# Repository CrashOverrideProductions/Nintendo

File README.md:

## Retro Console Parts

### **Project**: Replacement and Modification Parts for Retro Consoles 

<!-- Repo Cover Image -->

<!-- Repo Stats -->

### Details
The goal of this project is to have a collection of replacement and modification parts for retro game consoles.

<!-- To Do List -->
### Parts List
- [ ] Famicom Power Board (With Composite A/V Output)
- [x] Famicom / NES Controller PCB
- [x] Famicom HVC-NROM Cartride PCB
- [ ] SNES Controller PCB
- [ ] More to add (possibly a switch game cart pcb)

### Repo To Do List
- [ ] Tidy and Attribute Research Docs
- [ ] More to add as i think of it

<!-- Licencing Always at the Bottom -->
### Licencing 

**Creative Commons: Attribution - NonCommercial - ShareAlike 4.0 International (CC BY-NC-SA 4.0)**

**You are free to:**

**Share** — copy and redistribute the material in any medium or format

**Adapt** — remix, transform, and build upon the material

**Under the following terms:**

**Attribution** — You must give appropriate credit, provide a link to the license, and indicate if changes were made. You may do so in any reasonable manner, but not in any way that suggests the licensor endorses you or your use.

**NonCommercial** — You may not use the material for commercial purposes.

**ShareAlike** — If you remix, transform, or build upon the material, you must distribute your contributions under the same license as the original.

No additional restrictions — You may not apply legal terms or technological measures that legally restrict others from doing anything the license permits.

#####  One Last Note: 
I intent to be meticulous in using community generated documents and schematics where i cant easily reverse engineer things myself, under no circumstances will any Official/Leaked Manufacturer Interlectual Property be used in this project (e.g. Actual Schematics are covered by Copyright, however the circuit is not and therefore can be published if a third party person draws and publishes thier own reverse engineered schematic)

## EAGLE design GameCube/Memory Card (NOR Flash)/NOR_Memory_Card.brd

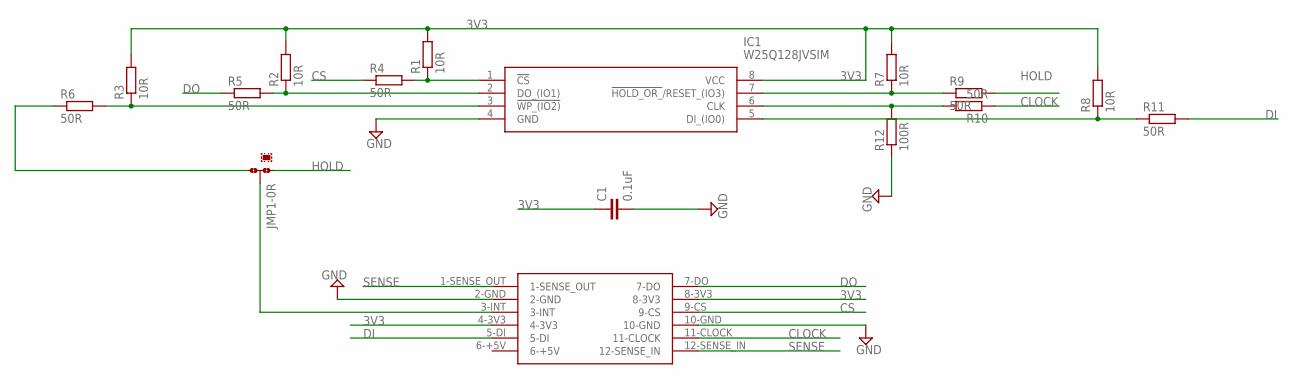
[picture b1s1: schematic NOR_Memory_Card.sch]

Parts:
C1: 0.1uF; C0805
IC1: W25Q128JVSIM; SOIC127P790X216-8N
JMP1: 0R-JUMPA; A0R-JMP
R1, R2, R3, R7, R8: 10R; R0805
R4, R5, R6, R9, R10, R11: 50R; R0805
R12: 100R; R0805
U$1: MEM_CARD_CONN

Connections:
3V3: C1.1, IC1.8 (VCC), R1.2, R2.2, R3.2, R7.2, R8.2, U$1.4-3V3, U$1.8-3V3
CLOCK: R10.1, U$1.11-CLOCK
CS: R4.1, U$1.9-CS
DI: R11.2, U$1.5-DI
DO: R5.1, U$1.7-DO
GND: C1.2, IC1.4 (GND), R12.1, U$1.2-GND, U$1.10-GND
HOLD: JMP1.1, R9.2
unnamed: IC1.7 (!HOLD_OR_!/RESET_(IO3)), R7.1, R9.1
unnamed: IC1.6 (CLK), R10.2, R12.2
unnamed: JMP1.3, R6.1
unnamed: IC1.3 (!WP_(IO2)), R3.1, R6.2
unnamed: IC1.5 (DI_(IO0)), R8.1, R11.1
unnamed: IC1.2 (DO_(IO1)), R2.1, R5.2
unnamed: IC1.1 (!CS), R1.1, R4.2
unnamed: JMP1.2, U$1.3-INT
SENSE: U$1.1-SENSE_OUT, U$1.12-SENSE_IN

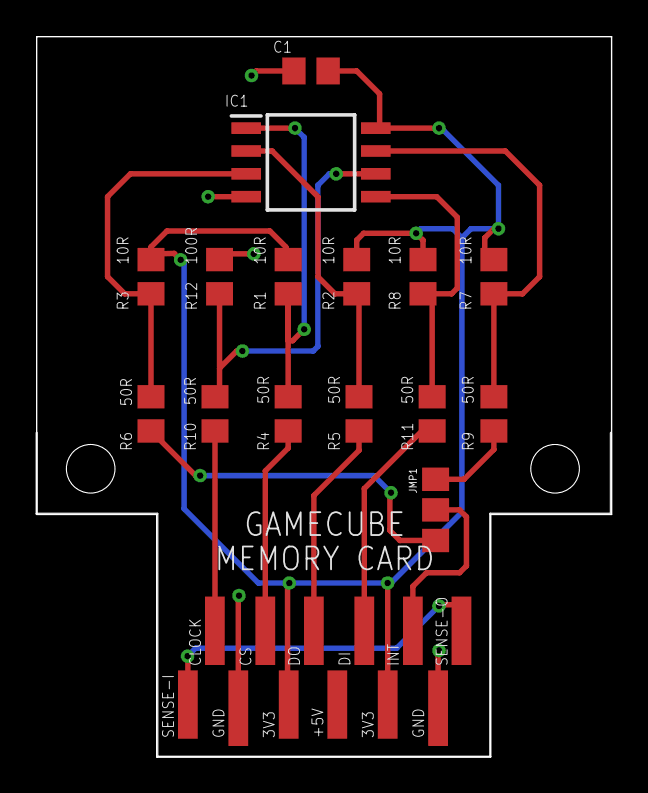
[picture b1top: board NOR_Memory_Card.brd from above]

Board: 2 copper layers, 31.9 x 40.0 mm, 16 parts (0 on the bottom side), 16 nets.

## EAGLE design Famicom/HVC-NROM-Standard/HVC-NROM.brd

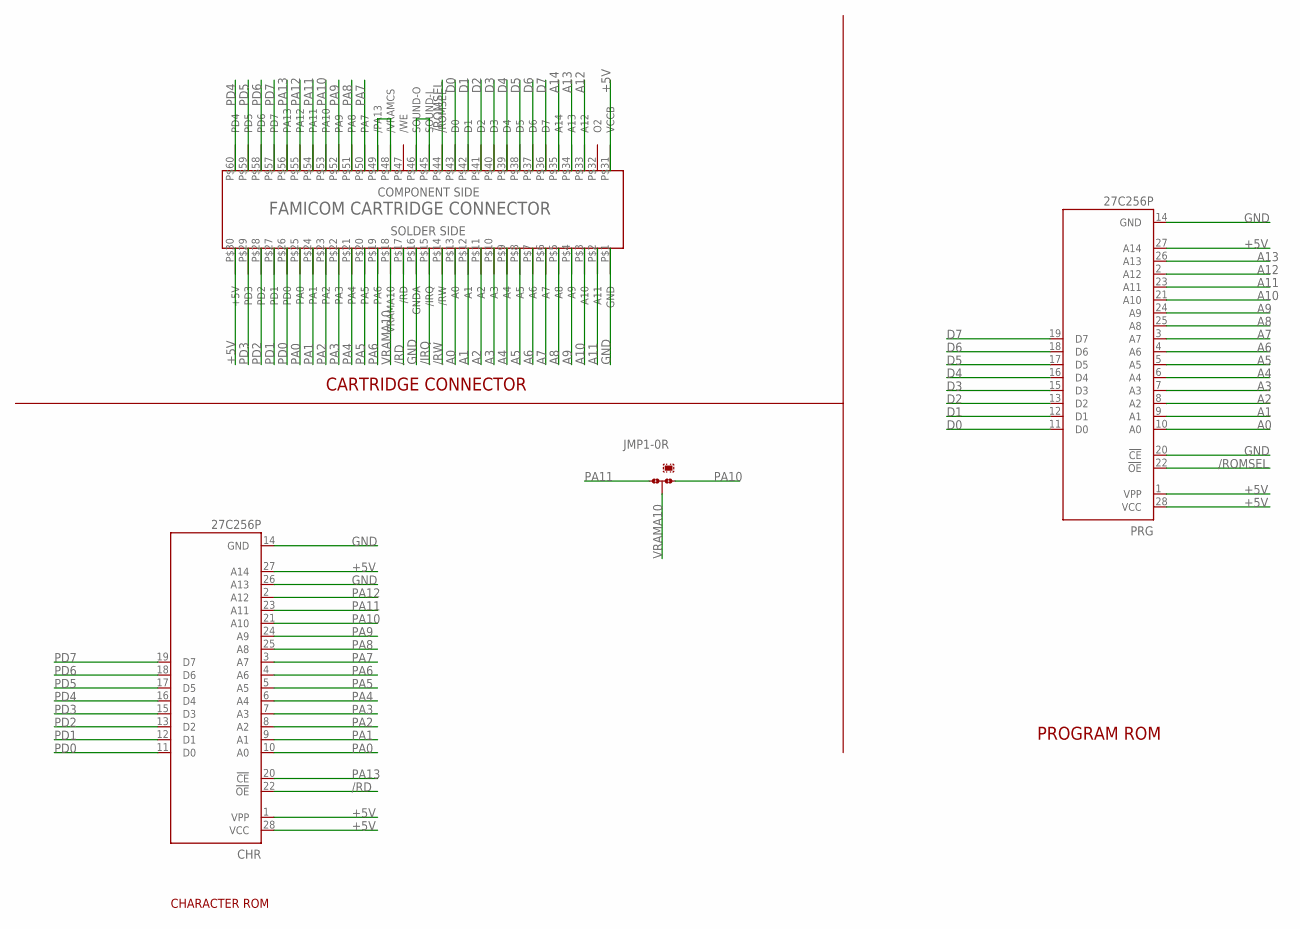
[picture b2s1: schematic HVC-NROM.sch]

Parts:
CHR: 27C256P; DIL28-6
JMP1: 0R-JUMPA; A0R-JMP
PRG: 27C256P; DIL28-6
U$1: FC-60-CART-PIN; FC-60-PIN-CART

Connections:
+5V: CHR.1 (VPP), CHR.27 (A14), CHR.28 (VCC), PRG.1 (VPP), PRG.27 (A14), PRG.28 (VCC), U$1.P$30 (+5V), U$1.P$31 (VCCB)
/IRQ: U$1.P$15 (/IRQ)
/RD: CHR.22 (!OE), U$1.P$17 (/RD)
/ROMSEL: PRG.22 (!OE), U$1.P$44 (/ROMSEL)
/RW: U$1.P$14 (/RW)
A0: PRG.10 (A0), U$1.P$13 (A0)
A1: PRG.9 (A1), U$1.P$12 (A1)
A2: PRG.8 (A2), U$1.P$11 (A2)
A3: PRG.7 (A3), U$1.P$10 (A3)
A4: PRG.6 (A4), U$1.P$9 (A4)
A5: PRG.5 (A5), U$1.P$8 (A5)
A6: PRG.4 (A6), U$1.P$7 (A6)
A7: PRG.3 (A7), U$1.P$6 (A7)
A8: PRG.25 (A8), U$1.P$5 (A8)
A9: PRG.24 (A9), U$1.P$4 (A9)
A10: PRG.21 (A10), U$1.P$3 (A10)
A11: PRG.23 (A11), U$1.P$2 (A11)
A12: PRG.2 (A12), U$1.P$33 (A12)
A13: PRG.26 (A13), U$1.P$34 (A13)
A14: U$1.P$35 (A14)
D0: PRG.11 (D0), U$1.P$43 (D0)
D1: PRG.12 (D1), U$1.P$42 (D1)
D2: PRG.13 (D2), U$1.P$41 (D2)
D3: PRG.15 (D3), U$1.P$40 (D3)
D4: PRG.16 (D4), U$1.P$39 (D4)
D5: PRG.17 (D5), U$1.P$38 (D5)
D6: PRG.18 (D6), U$1.P$37 (D6)
D7: PRG.19 (D7), U$1.P$36 (D7)
GND: CHR.14 (GND), CHR.26 (A13), PRG.14 (GND), PRG.20 (!CE), U$1.P$1 (GND), U$1.P$16 (GNDA)
unnamed: U$1.P$45 (SOUND-I), U$1.P$46 (SOUND-O)
unnamed: U$1.P$48 (/VRAMCS), U$1.P$49 (/PA13)
PA0: CHR.10 (A0), U$1.P$25 (PA0)
PA1: CHR.9 (A1), U$1.P$24 (PA1)
PA2: CHR.8 (A2), U$1.P$23 (PA2)
PA3: CHR.7 (A3), U$1.P$22 (PA3)
PA4: CHR.6 (A4), U$1.P$21 (PA4)
PA5: CHR.5 (A5), U$1.P$20 (PA5)
PA6: CHR.4 (A6), U$1.P$19 (PA6)
PA7: CHR.3 (A7), U$1.P$50 (PA7)
PA8: CHR.25 (A8), U$1.P$51 (PA8)
PA9: CHR.24 (A9), U$1.P$52 (PA9)
PA10: CHR.21 (A10), JMP1.1, U$1.P$53 (PA10)
PA11: CHR.23 (A11), JMP1.3, U$1.P$54 (PA11)
PA12: CHR.2 (A12), U$1.P$55 (PA12)
PA13: CHR.20 (!CE), U$1.P$56 (PA13)
PD0: CHR.11 (D0), U$1.P$26 (PD0)
PD1: CHR.12 (D1), U$1.P$27 (PD1)
PD2: CHR.13 (D2), U$1.P$28 (PD2)
PD3: CHR.15 (D3), U$1.P$29 (PD3)
PD4: CHR.16 (D4), U$1.P$60 (PD4)
PD5: CHR.17 (D5), U$1.P$59 (PD5)
PD6: CHR.18 (D6), U$1.P$58 (PD6)
PD7: CHR.19 (D7), U$1.P$57 (PD7)
VRAMA10: JMP1.2, U$1.P$18 (VRAMA10)

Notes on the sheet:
PROGRAM ROM
CHARACTER ROM
CARTRIDGE CONNECTOR

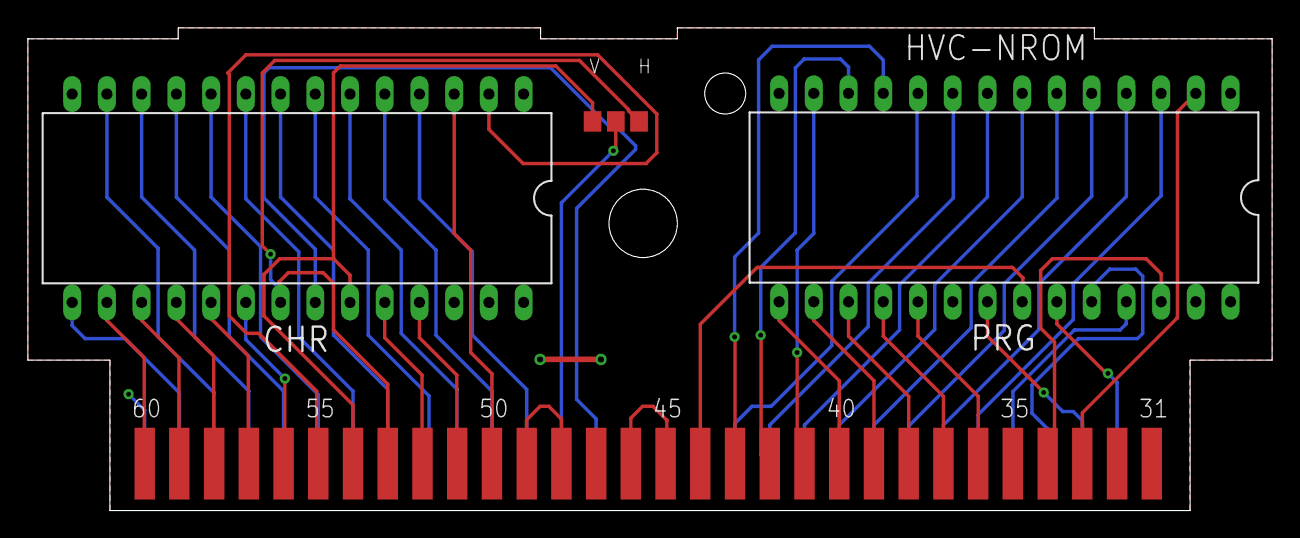
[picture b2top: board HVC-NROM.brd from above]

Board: 2 copper layers, 91.0 x 35.3 mm, 4 parts (0 on the bottom side), 51 nets.

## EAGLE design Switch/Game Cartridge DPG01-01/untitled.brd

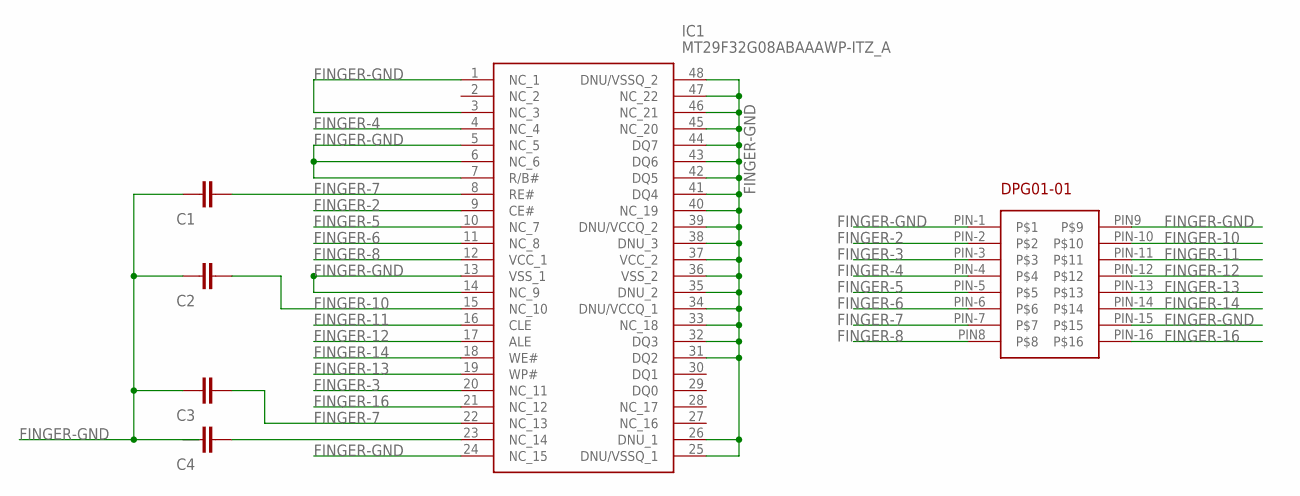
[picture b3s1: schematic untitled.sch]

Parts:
C1, C2, C3, C4: C-EUC0402; C0402
IC1: MT29F32G08ABAAAWP-ITZ_A; SOP50P2000X120-48N
U$1: DPG01-01

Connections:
FINGER-2: IC1.9 (CE#), U$1.PIN-2
FINGER-3: IC1.20 (NC_11), U$1.PIN-3
FINGER-4: IC1.4 (NC_4), U$1.PIN-4
FINGER-5: IC1.10 (NC_7), U$1.PIN-5
FINGER-6: IC1.11 (NC_8), U$1.PIN-6
FINGER-7: C1.1, C3.1, IC1.8 (RE#), IC1.22 (NC_13), U$1.PIN-7
FINGER-8: IC1.12 (VCC_1), U$1.PIN8
FINGER-10: C2.1, IC1.15 (NC_10), U$1.PIN-10
FINGER-11: IC1.16 (CLE), U$1.PIN-11
FINGER-12: IC1.17 (ALE), U$1.PIN-12
FINGER-13: IC1.19 (WP#), U$1.PIN-13
FINGER-14: IC1.18 (WE#), U$1.PIN-14
FINGER-16: IC1.21 (NC_12), U$1.PIN-16
FINGER-GND: C1.2, C2.2, C3.2, C4.2, IC1.1 (NC_1), IC1.3 (NC_3), IC1.5 (NC_5), IC1.6 (NC_6), IC1.7 (R/B#), IC1.13 (VSS_1), IC1.14 (NC_9), IC1.24 (NC_15), IC1.25 (DNU/VSSQ_1), IC1.26 (DNU_1), IC1.31 (DQ2), IC1.32 (DQ3), IC1.33 (NC_18), IC1.34 (DNU/VCCQ_1), IC1.35 (DNU_2), IC1.36 (VSS_2), IC1.37 (VCC_2), IC1.38 (DNU_3), IC1.39 (DNU/VCCQ_2), IC1.40 (NC_19), IC1.41 (DQ4), IC1.42 (DQ5), IC1.43 (DQ6), IC1.44 (DQ7), IC1.45 (NC_20), IC1.46 (NC_21), IC1.47 (NC_22), IC1.48 (DNU/VSSQ_2), U$1.PIN9, U$1.PIN-1, U$1.PIN-15
unnamed: C4.1, IC1.23 (NC_14)

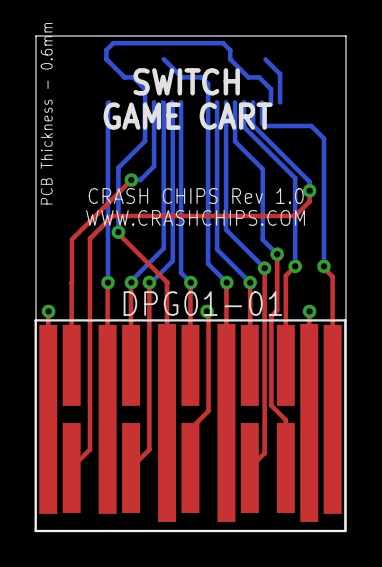
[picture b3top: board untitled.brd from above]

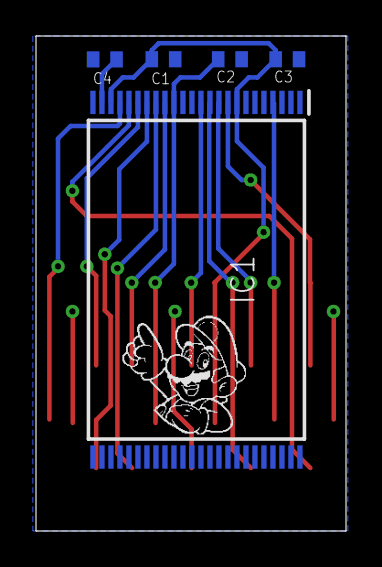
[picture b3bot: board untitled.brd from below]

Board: 2 copper layers, 17.2 x 27.5 mm, 6 parts (5 on the bottom side), 15 nets.

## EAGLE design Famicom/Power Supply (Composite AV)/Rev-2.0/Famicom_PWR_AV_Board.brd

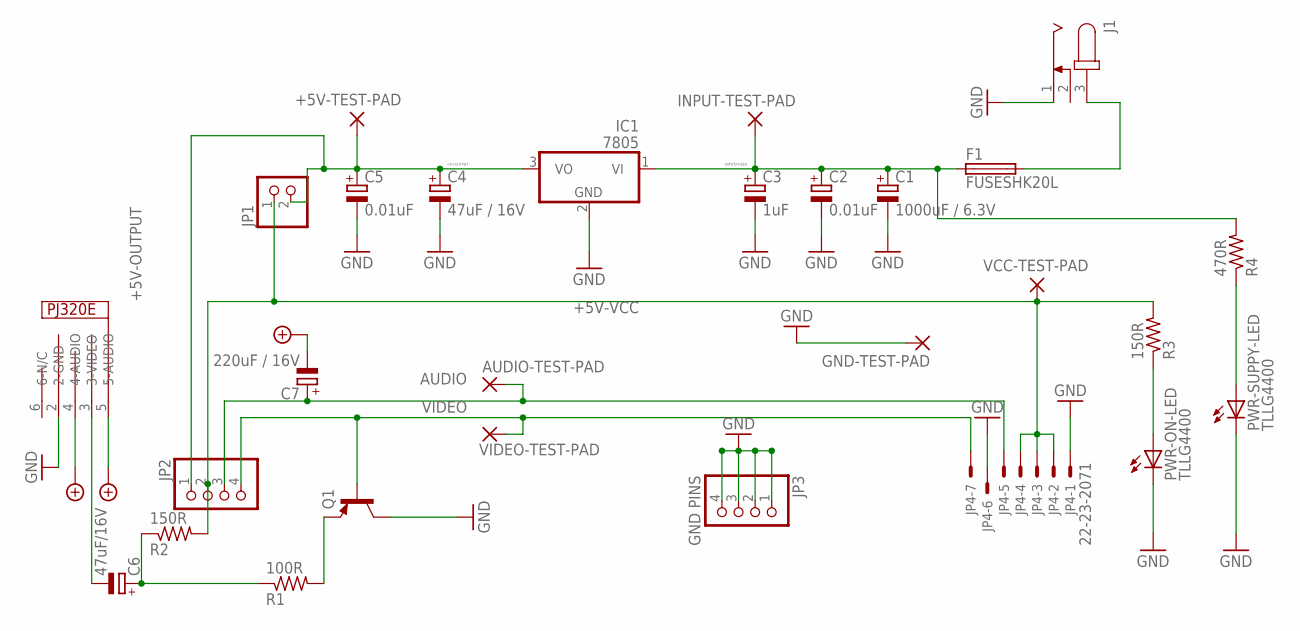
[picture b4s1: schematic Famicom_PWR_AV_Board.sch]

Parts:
+5V-TEST-PAD: WIREPAD2,15/1,0; 2,15/1,0
AUDIO-TEST-PAD: WIREPAD2,15/1,0; 2,15/1,0
C1: 1000uF / 6.3V; TAP5-45
C2, C5: 0.01uF; TAP5-45
C3: 1uF; TAP5-45
C4: 47uF / 16V; TAP5-45
C6: 47uF/16V; TAP5-45
C7: 220uF / 16V; TAP5-45
F1: FUSESHK20L; SHK20L
GND-TEST-PAD: WIREPAD2,15/1,0; 2,15/1,0
IC1: 7805; TO220V
INPUT-TEST-PAD: WIREPAD2,15/1,0; 2,15/1,0
J1: JACK-PLUG0; SPC4077
JP1: PINHD-1X2; 1X02
JP2: PINHD-1X4; 1X04
JP3: GND PINS; 1X04
JP4: 22-23-2071
PWR-ON-LED: TLLG4400; LED3MM
PWR-SUPPY-LED: TLLG4400; LED3MM
Q1: MPSA56-TO92; TO92-CBE
R1: 100R; 0204/7
R2, R3: 150R; 0204/7
R4: 470R; 0204/7
U$2: PJ320E
VCC-TEST-PAD: WIREPAD2,15/1,0; 2,15/1,0
VIDEO-TEST-PAD: WIREPAD2,15/1,0; 2,15/1,0

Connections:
+5V-OUTPUT: +5V-TEST-PAD.1, C4.+, C5.+, IC1.3 (VO), JP1.2, JP2.1
+5V-VCC: JP1.1, JP2.2, JP4.2, JP4.3, JP4.4, R2.2, R3.2, VCC-TEST-PAD.1
+9V-INPUT-UNFUSED: F1.2A (2), J1.3
AUDIO: AUDIO-TEST-PAD.1, C7.+, JP2.3, JP4.5
AUDIO_OUTPUT: C7.-, U$2.4 (4-AUDIO), U$2.5 (5-AUDIO)
GND: C1.-, C2.-, C3.-, C4.-, C5.-, GND-TEST-PAD.1, IC1.2 (GND), J1.1, JP3.1, JP3.2, JP3.3, JP3.4, JP4.1, JP4.6, PWR-ON-LED.K (C), PWR-SUPPY-LED.K (C), Q1.C, U$2.2 (2-GND)
INPUT|FUSED: C1.+, C2.+, C3.+, F1.1A (1), IC1.1 (VI), INPUT-TEST-PAD.1, R4.2
ON_LED: PWR-ON-LED.A, R3.1
SUPPLY_LED: PWR-SUPPY-LED.A, R4.1
VIDEO: JP2.4, JP4.7, Q1.B, VIDEO-TEST-PAD.1
VIDEO_AMP: C6.+, R1.1, R2.1
VIDEO_OUTPUT: C6.-, U$2.3 (3-VIDEO)
VIDEO_PREAMP: Q1.E, R1.2

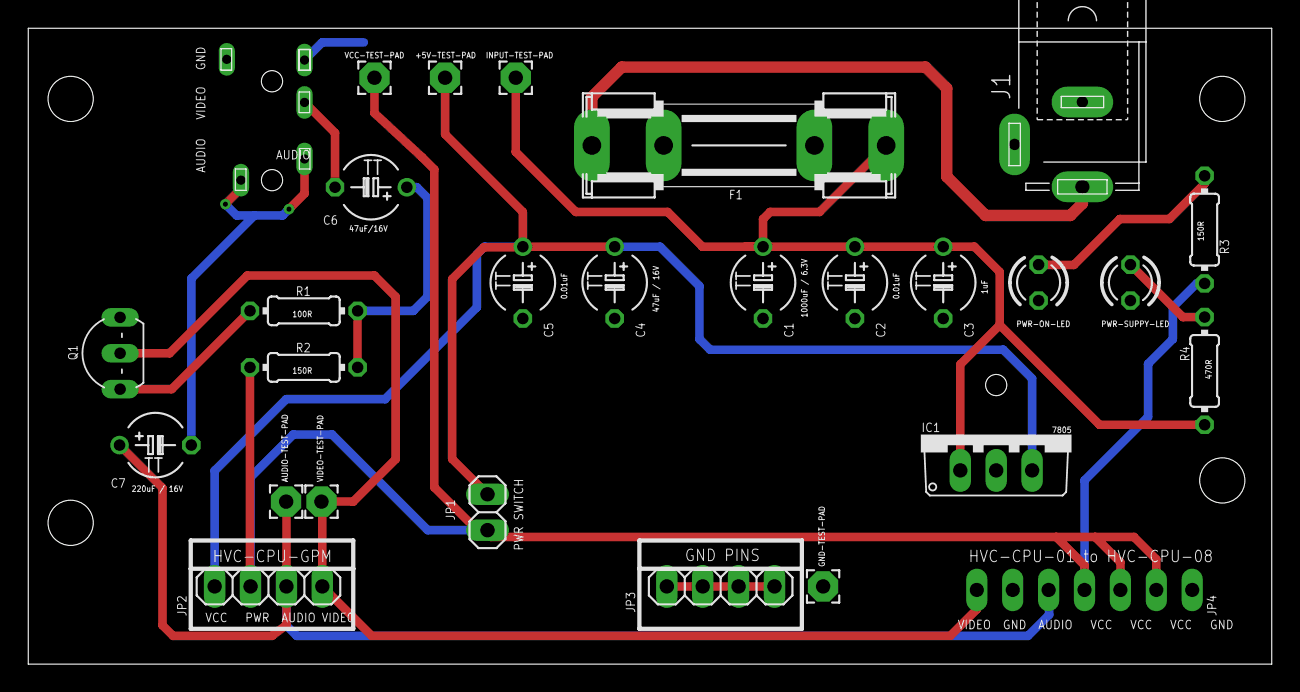
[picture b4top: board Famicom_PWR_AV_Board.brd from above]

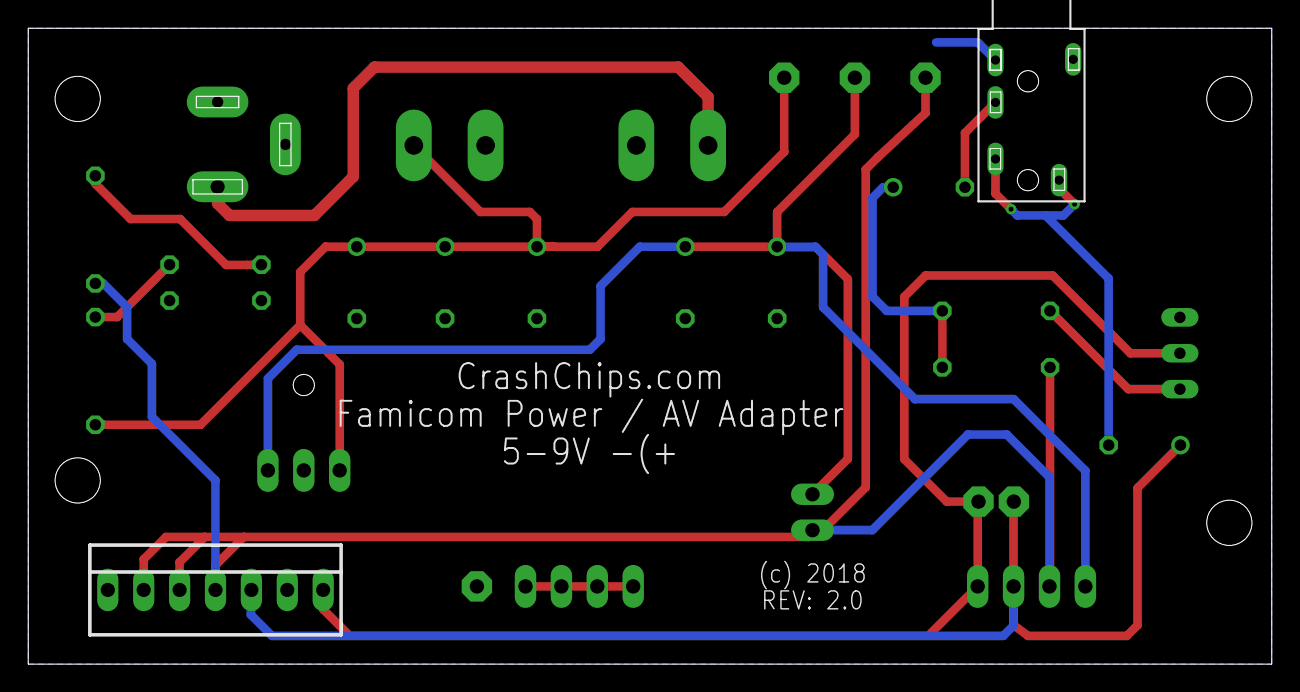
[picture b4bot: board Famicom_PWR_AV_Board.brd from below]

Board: 2 copper layers, 87.9 x 44.9 mm, 28 parts (2 on the bottom side), 13 nets.

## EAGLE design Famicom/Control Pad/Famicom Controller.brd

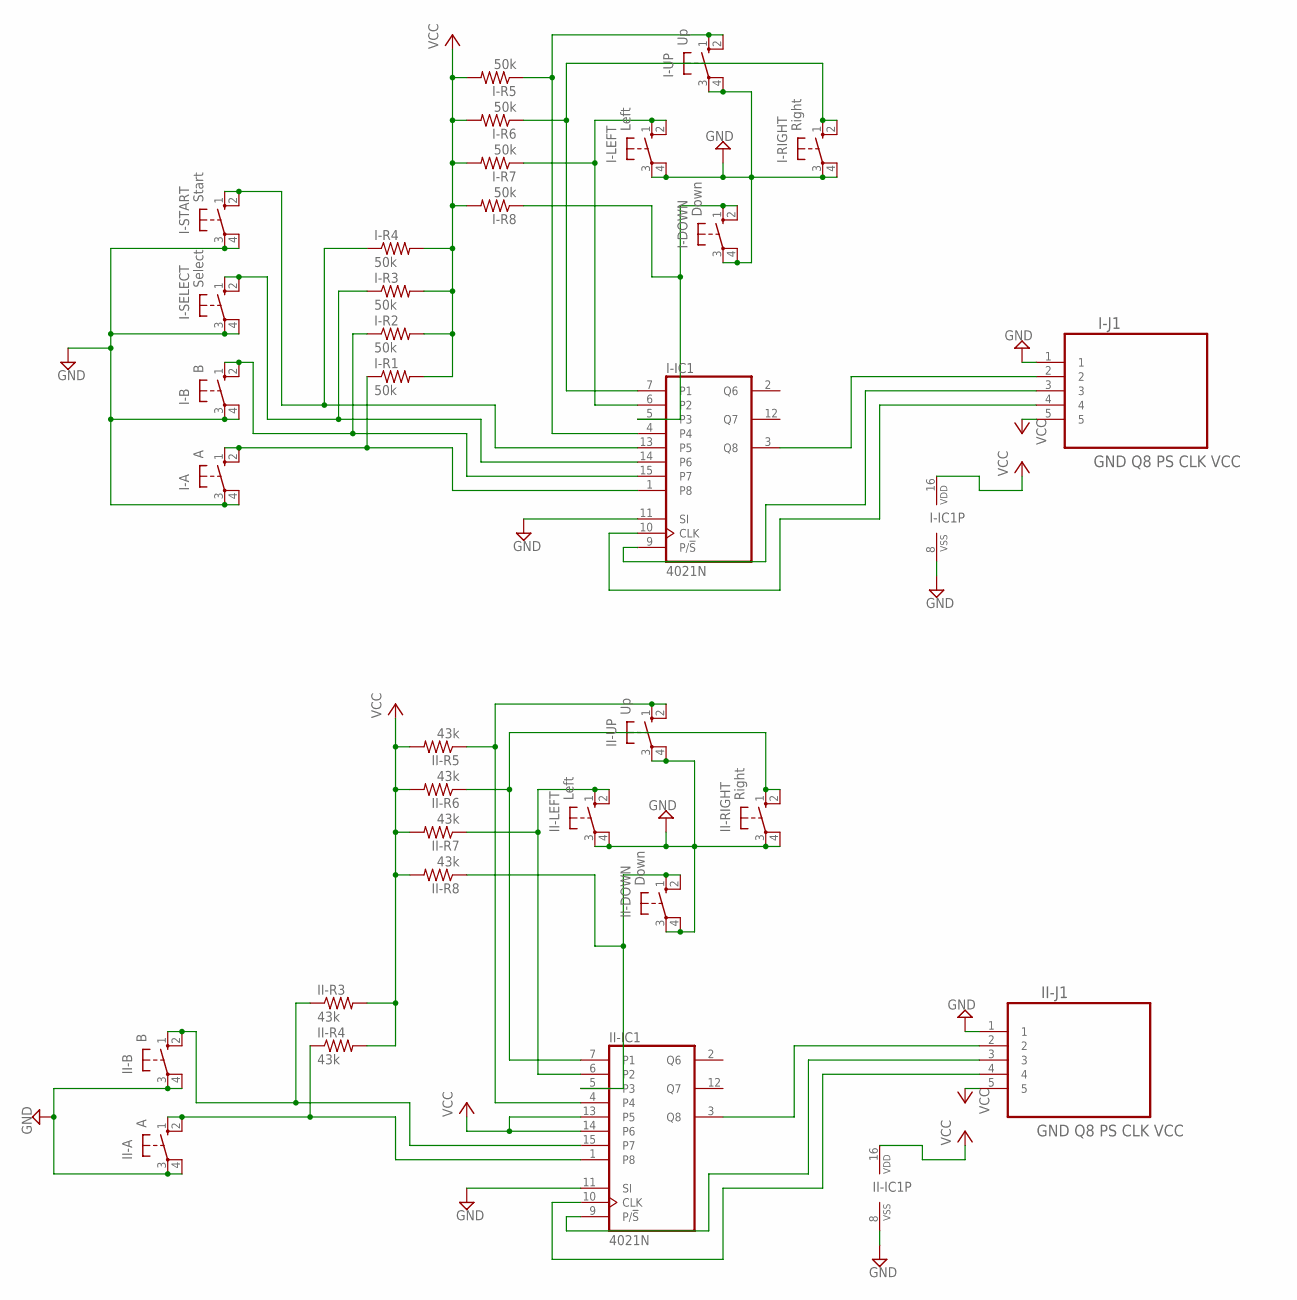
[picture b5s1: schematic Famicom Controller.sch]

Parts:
I-A: A; B3F-10XX
I-B: B; B3F-10XX
I-DOWN: Down; B3F-10XX
I-IC1: 4021N; DIL16
I-J1: GND Q8 PS CLK VCC; SAMTEC_TLW-105-05-G-S
I-LEFT: Left; B3F-10XX
I-R1, I-R2, I-R3, I-R4, I-R5, I-R6, I-R7, I-R8: 50k; 0207/7
I-RIGHT: Right; B3F-10XX
I-SELECT: Select; B3F-10XX
I-START: Start; B3F-10XX
I-UP: Up; B3F-10XX
II-A: A; B3F-10XX
II-B: B; B3F-10XX
II-DOWN: Down; B3F-10XX
II-IC1: 4021N; DIL16
II-J1: GND Q8 PS CLK VCC; SAMTEC_TLW-105-05-G-S
II-LEFT: Left; B3F-10XX
II-R3, II-R4, II-R5, II-R6, II-R7, II-R8: 43k; 0207/7
II-RIGHT: Right; B3F-10XX
II-UP: Up; B3F-10XX

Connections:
GND: I-A.3, I-A.4 (P1), I-B.3, I-B.4 (P1), I-DOWN.3, I-DOWN.4 (P1), I-IC1.8 (VSS), I-IC1.11 (SI), I-J1.1, I-LEFT.3, I-LEFT.4 (P1), I-RIGHT.3, I-RIGHT.4 (P1), I-SELECT.3, I-SELECT.4 (P1), I-START.3, I-START.4 (P1), I-UP.3, I-UP.4 (P1), II-A.3, II-A.4 (P1), II-B.3, II-B.4 (P1), II-DOWN.3, II-DOWN.4 (P1), II-IC1.8 (VSS), II-IC1.11 (SI), II-J1.1, II-LEFT.3, II-LEFT.4 (P1), II-RIGHT.3, II-RIGHT.4 (P1), II-UP.3, II-UP.4 (P1)
unnamed: I-IC1.3 (Q8), I-J1.2
unnamed: I-IC1.9 (P/!S), I-J1.3
unnamed: I-IC1.10 (CLK), I-J1.4
unnamed: I-DOWN.1 (S), I-DOWN.2 (S1), I-IC1.5 (P3), I-R8.1
unnamed: I-IC1.4, I-R5.1, I-UP.1 (S), I-UP.2 (S1)
unnamed: I-IC1.6 (P2), I-LEFT.1 (S), I-LEFT.2 (S1), I-R7.1
unnamed: I-B.1 (S), I-B.2 (S1), I-IC1.15 (P7), I-R2.1
unnamed: I-A.1 (S), I-A.2 (S1), I-IC1.1 (P8), I-R1.1
unnamed: I-IC1.13 (P5), I-R4.1, I-START.1 (S), I-START.2 (S1)
unnamed: I-IC1.14 (P6), I-R3.1, I-SELECT.1 (S), I-SELECT.2 (S1)
unnamed: I-IC1.7 (P1), I-R6.1, I-RIGHT.1 (S), I-RIGHT.2 (S1)
unnamed: II-IC1.3 (Q8), II-J1.2
unnamed: II-IC1.9 (P/!S), II-J1.3
unnamed: II-IC1.10 (CLK), II-J1.4
unnamed: II-B.1 (S), II-B.2 (S1), II-IC1.15 (P7), II-R3.1
unnamed: II-A.1 (S), II-A.2 (S1), II-IC1.1 (P8), II-R4.1
unnamed: II-DOWN.1 (S), II-DOWN.2 (S1), II-IC1.5 (P3), II-R8.1
unnamed: II-IC1.4, II-R5.1, II-UP.1 (S), II-UP.2 (S1)
unnamed: II-IC1.6 (P2), II-LEFT.1 (S), II-LEFT.2 (S1), II-R7.1
unnamed: II-IC1.7 (P1), II-R6.1, II-RIGHT.1 (S), II-RIGHT.2 (S1)
VCC: I-IC1.16 (VDD), I-J1.5, I-R1.2, I-R2.2, I-R3.2, I-R4.2, I-R5.2, I-R6.2, I-R7.2, I-R8.2, II-IC1.13 (P5), II-IC1.14 (P6), II-IC1.16 (VDD), II-J1.5, II-R3.2, II-R4.2, II-R5.2, II-R6.2, II-R7.2, II-R8.2

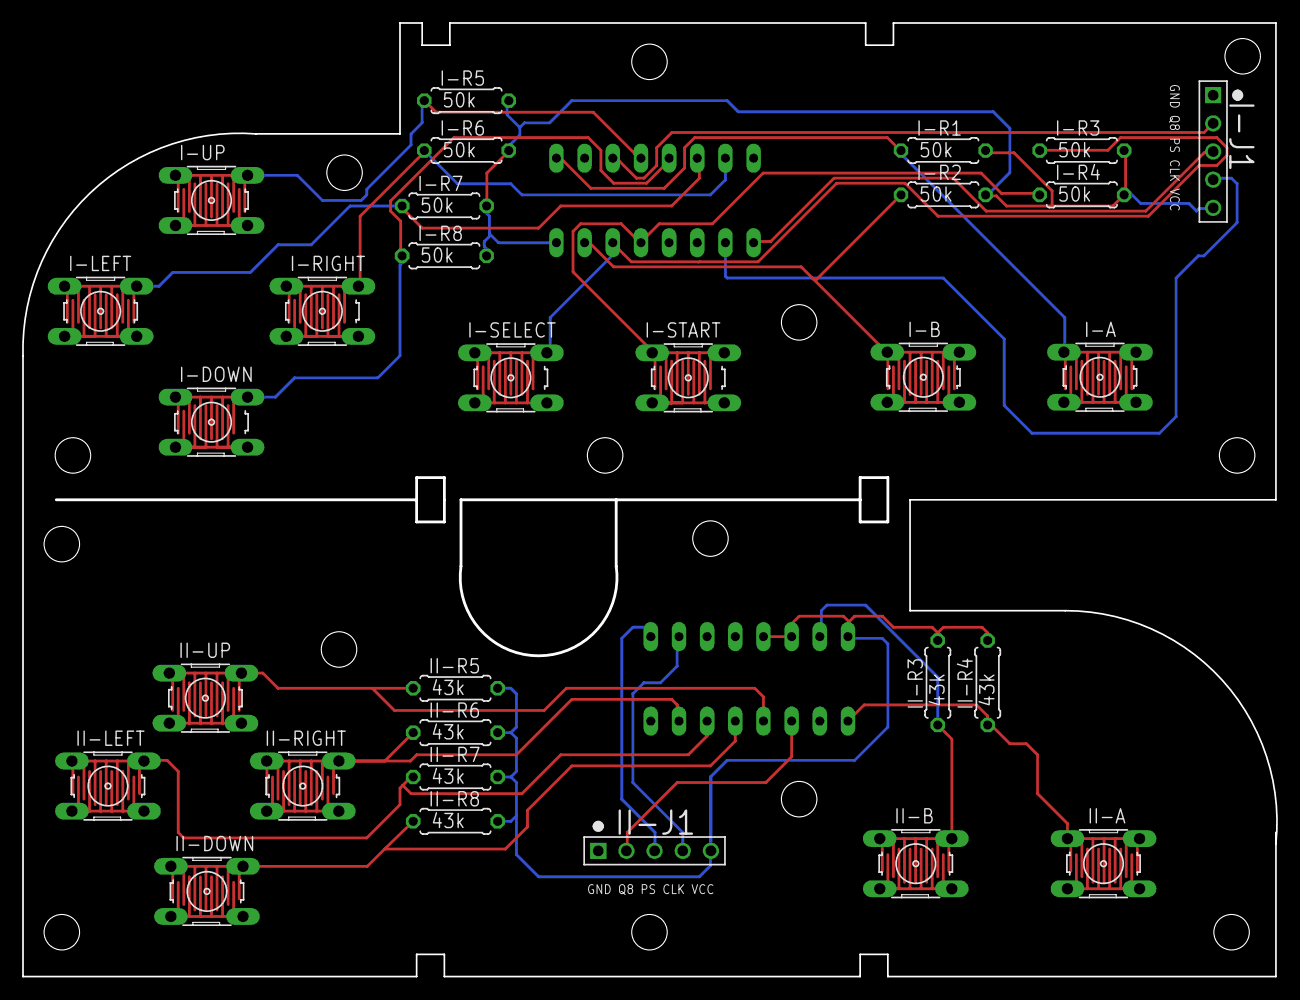
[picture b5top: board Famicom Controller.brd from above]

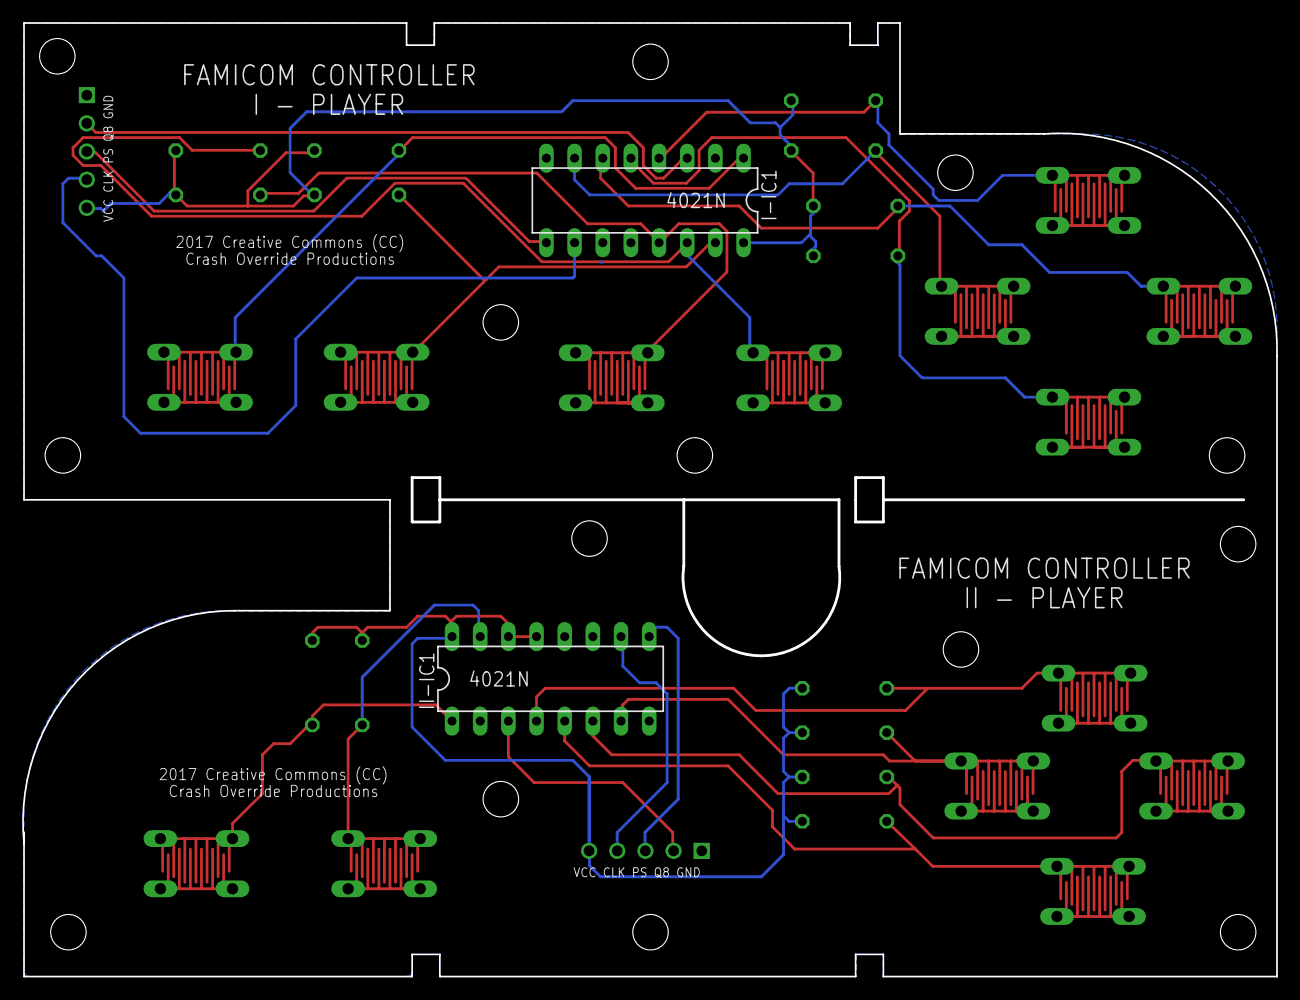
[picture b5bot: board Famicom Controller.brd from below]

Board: 2 copper layers, 113.0 x 85.9 mm, 32 parts (2 on the bottom side), 22 nets.

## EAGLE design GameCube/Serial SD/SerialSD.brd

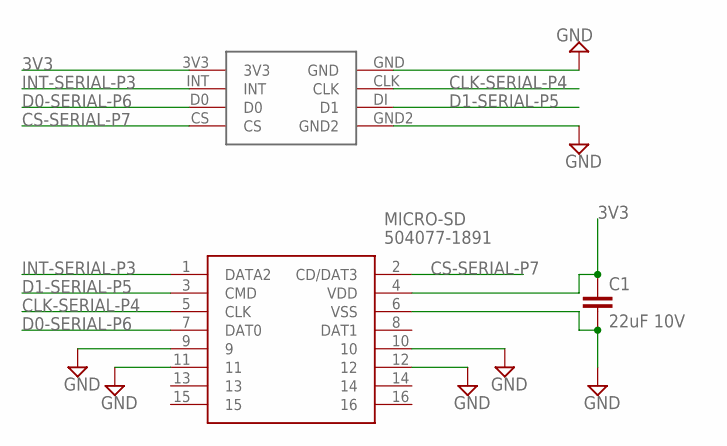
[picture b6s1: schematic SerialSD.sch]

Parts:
C1: 22uF 10V; C0805
MICRO-SD: 504077-1891; 5040771891
U$1: SERAIL1; SERIAL1

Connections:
3V3: C1.1, MICRO-SD.4 (VDD), U$1.3V3
CLK-SERIAL-P4: MICRO-SD.5 (CLK), U$1.CLK
CS-SERIAL-P7: MICRO-SD.2 (CD/DAT3), U$1.CS
D0-SERIAL-P6: MICRO-SD.7 (DAT0), U$1.D0
D1-SERIAL-P5: MICRO-SD.3 (CMD), U$1.DI (D1)
GND: C1.2, MICRO-SD.6 (VSS), MICRO-SD.9, MICRO-SD.10, MICRO-SD.11, MICRO-SD.12, U$1.GND, U$1.GND2
INT-SERIAL-P3: MICRO-SD.1 (DATA2), U$1.INT

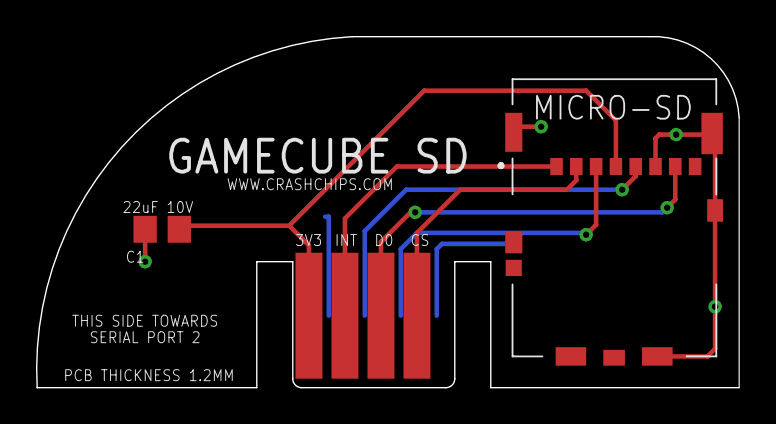
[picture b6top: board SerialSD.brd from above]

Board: 2 copper layers, 39.0 x 19.5 mm, 3 parts (0 on the bottom side), 7 nets.

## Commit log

2021-06-28 Create Repo

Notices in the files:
Famicom/Control Pad/Famicom Controller.brd:
2017 Creative Commons (CC)
Famicom/Power Supply (Composite AV)/Rev-2.0/Famicom_PWR_AV_Board.brd:
(c) 2018
README.md:
License: CC-BY-NC-SA-4.0
